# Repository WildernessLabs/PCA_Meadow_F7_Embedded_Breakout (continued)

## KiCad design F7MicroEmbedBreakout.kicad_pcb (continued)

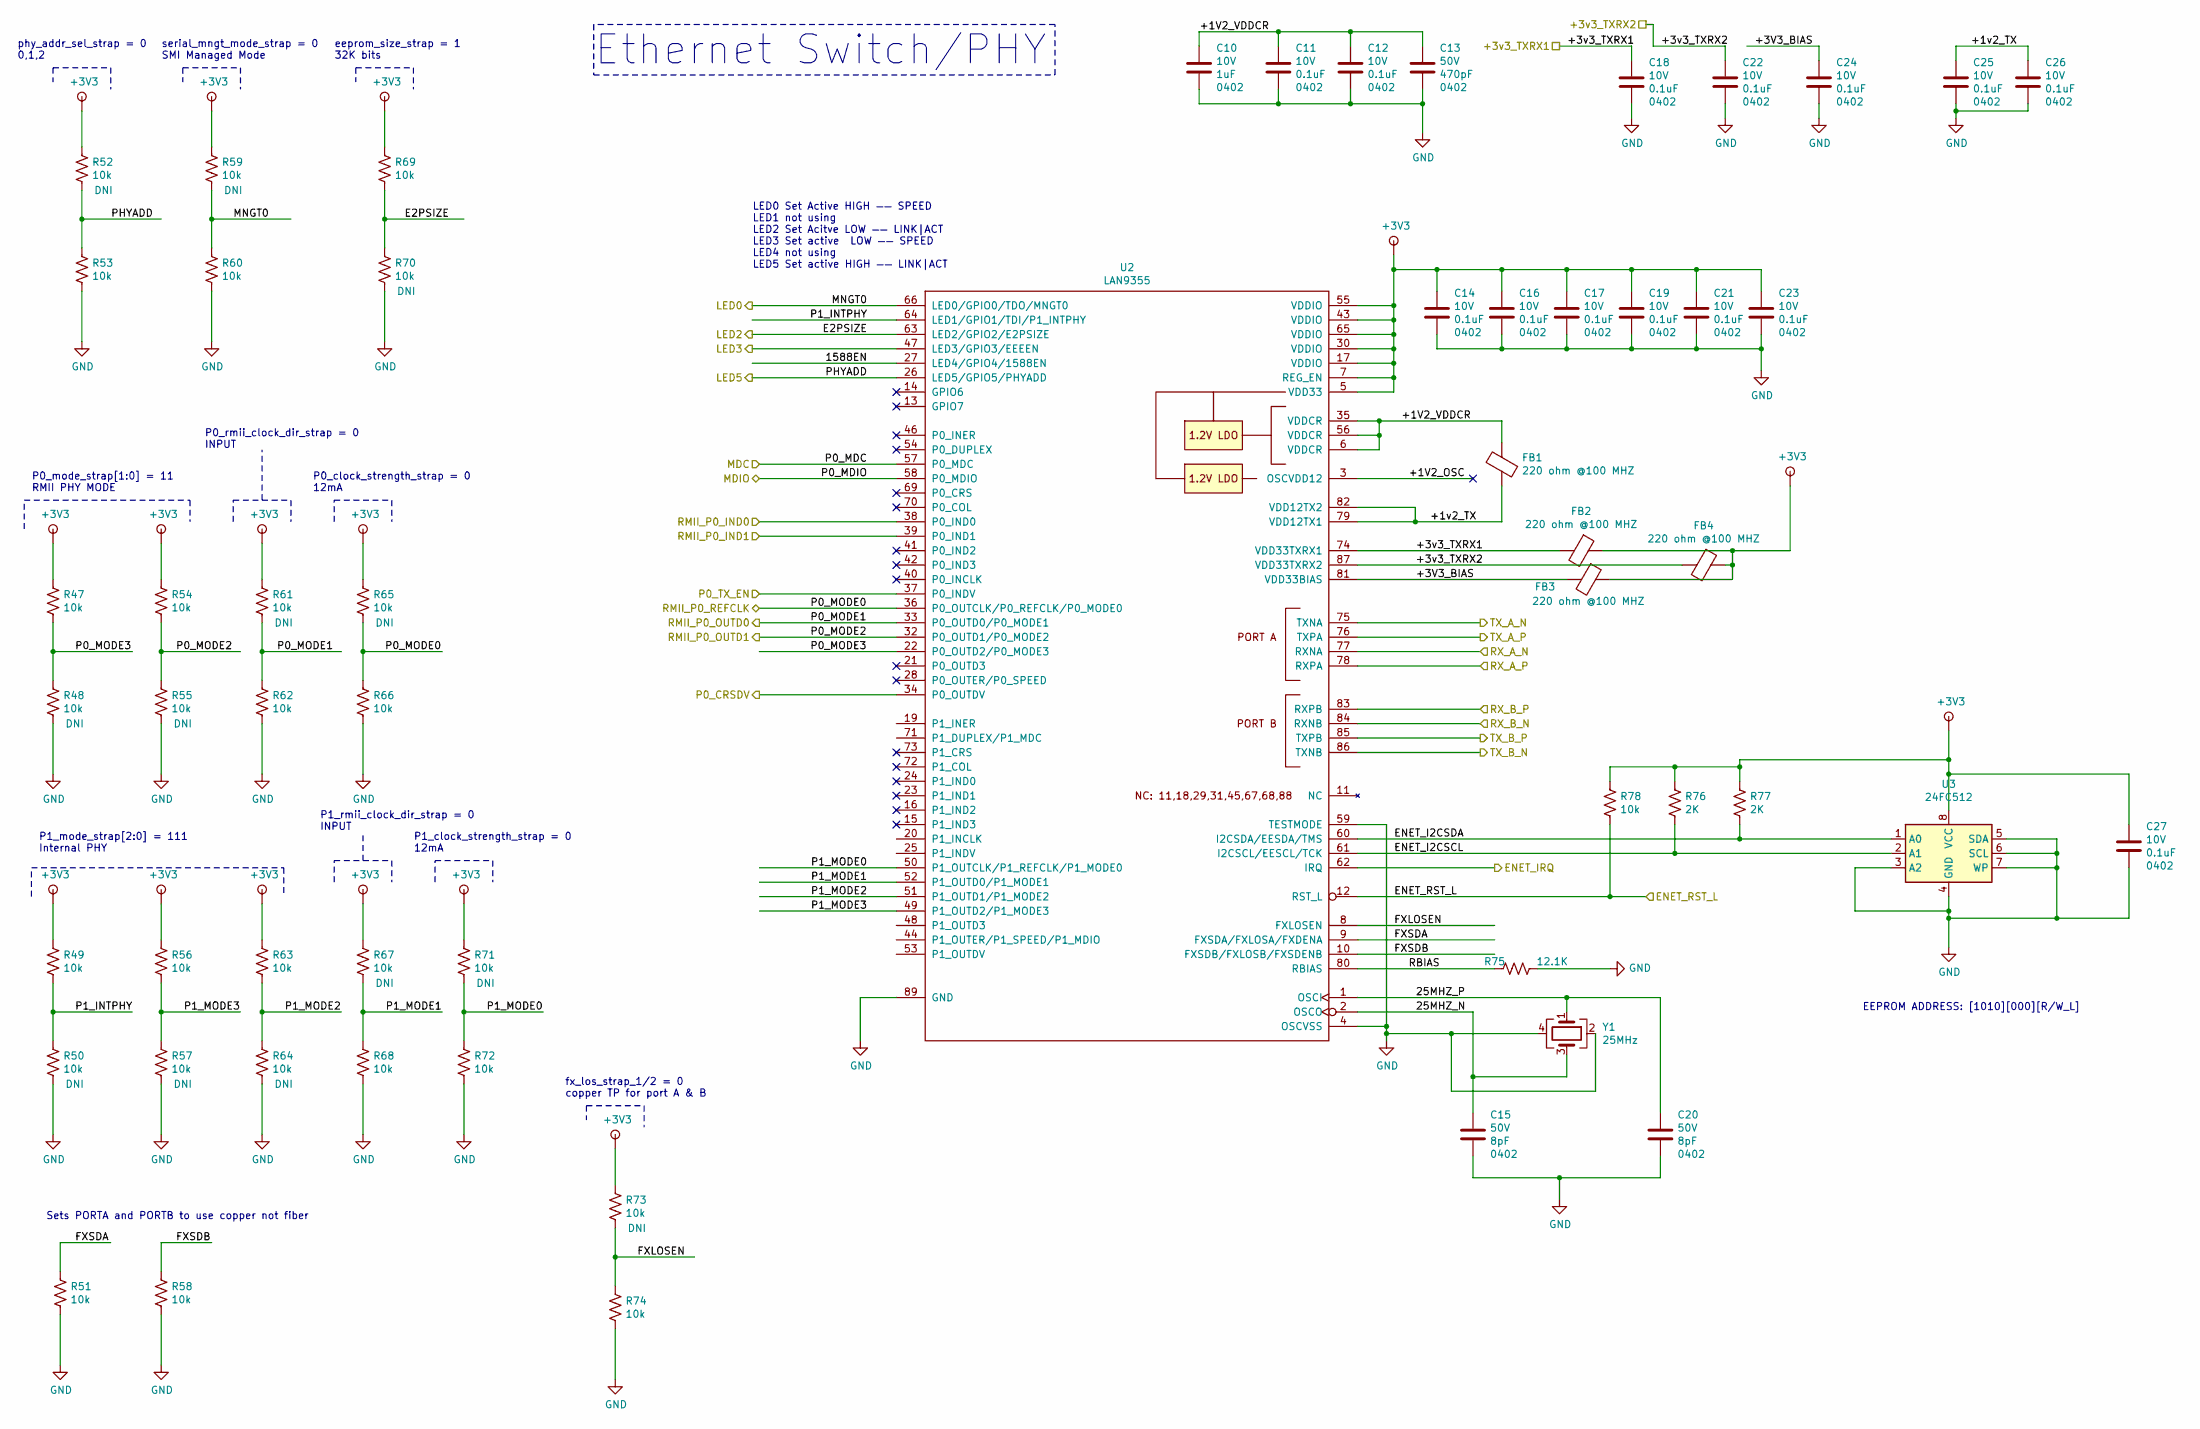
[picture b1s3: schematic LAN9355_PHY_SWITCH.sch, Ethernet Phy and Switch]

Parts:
C10: C_0402_1UF_10V_X5R; C_0402_1005Metric; Voltage 10V; Tolerance 20%
C11, C12, C14, C16, C17, C18, C19, C21, C22, C23, C24, C25, C26, C27: C_0402_0.1UF_10V_X5R; C_0402_1005Metric; Voltage 10V; Tolerance 20%
C13: C_0402_470pF_50V_X5R; C_0402_1005Metric; Voltage 50V; Tolerance 10%
C15, C20: C_0402_8pF_50V_X5R; C_0402_1005Metric; Voltage 50V; Tolerance 0.25pF
FB1, FB2, FB3, FB4: BEAD_BLM18KG221SN1D; R_0603
R47, R48, R49, R50, R51, R52, R53, R54, R55, R56, R57, R58, R59, R60, R61, R62, R63, R64, R65, R66, R67, R68, R69, R70, R71, R72, R73, R74, R78: R_10k_1%_0603; R_0402_1005Metric; Tolerance 1%
R75: R_12K1_1%_0402; R_0402_1005Metric; Tolerance 1%
R76, R77: R_2K_1%_0402; R_0402_1005Metric; Tolerance 1%
U2: LAN9355; QFN-88_EP_12x12_Pitch0.5mm
U3: 24FC512; TSSOP-8_4.4x3mm_P0.65mm
Y1: ABM12W-25.0000MHZ-6-B1U-T3; XTAL_ABM12W-24.0000MHZ-6-B1U-T3

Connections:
+3V3: C14.1, C16.1, C17.1, C19.1, C21.1, C23.1, C27.1, FB2.1, FB3.1, FB4.1, R47.1, R49.1, R52.1, R54.1, R56.1, R59.1, R61.1, R63.1, R65.1, R67.1, R69.1, R71.1, R73.1, R76.1, R77.1, R78.1, U2.5 (VDD33), U2.7 (REG_EN), U2.17 (VDDIO), U2.30 (VDDIO), U2.43 (VDDIO), U2.55 (VDDIO), U2.65 (VDDIO), U3.8 (VCC); also elsewhere on the board
/ENET_SWITCH_PHY/25MHZ_N: C15.1, U2.2 (OSCO), Y1.3
/ENET_SWITCH_PHY/25MHZ_P: C20.1, U2.1 (OSCI), Y1.1
/ENET_SWITCH_PHY/1588EN: U2.27 (LED4/GPIO4/1588EN)
/ENET_SWITCH_PHY/+1V2_OSC: U2.3 (OSCVDD12)
/ENET_SWITCH_PHY/+1V2_VDDCR: C10.1, C11.1, C12.1, C13.1, FB1.2, U2.6 (VDDCR), U2.35 (VDDCR), U2.56 (VDDCR)
/ENET_SWITCH_PHY/+1v2_TX: C25.1, C26.1, FB1.1, U2.79 (VDD12TX1), U2.82 (VDD12TX2)
/ENET_SWITCH_PHY/+3V3_BIAS: C24.1, FB3.2, U2.81 (VDD33BIAS)
/ENET_SWITCH_PHY/+3v3_TXRX1: C18.1, FB2.2, U2.74 (VDD33TXRX1); also elsewhere on the board
/ENET_SWITCH_PHY/+3v3_TXRX2: C22.1, FB4.2, U2.87 (VDD33TXRX2); also elsewhere on the board
/ENET_SWITCH_PHY/ENET_I2CSCL: R76.2, U2.61 (I2CSCL/EESCL/TCK), U3.2 (A1)
/ENET_SWITCH_PHY/ENET_I2CSDA: R77.2, U2.60 (I2CSDA/EESDA/TMS), U3.1 (A0)
/ENET_SWITCH_PHY/FXLOSEN: R73.2, R74.1, U2.8 (FXLOSEN)
/ENET_SWITCH_PHY/FXSDA: R51.1, U2.9 (FXSDA/FXLOSA/FXDENA)
/ENET_SWITCH_PHY/FXSDB: R58.1, U2.10 (FXSDB/FXLOSB/FXSDENB)
/ENET_SWITCH_PHY/P0_MODE3: R47.2, R48.1, U2.22 (P0_OUTD2/P0_MODE3)
/ENET_SWITCH_PHY/P1_INTPHY: R49.2, R50.1, U2.64 (LED1/GPIO1/TDI/P1_INTPHY)
/ENET_SWITCH_PHY/P1_MODE0: R71.2, R72.1, U2.50 (P1_OUTCLK/P1_REFCLK/P1_MODE0)
/ENET_SWITCH_PHY/P1_MODE1: R67.2, R68.1, U2.52 (P1_OUTD0/P1_MODE1)
/ENET_SWITCH_PHY/P1_MODE2: R63.2, R64.1, U2.51 (P1_OUTD1/P1_MODE2)
/ENET_SWITCH_PHY/P1_MODE3: R56.2, R57.1, U2.49 (P1_OUTD2/P1_MODE3)
/ENET_SWITCH_PHY/RBIAS: R75.2, U2.80 (RBIAS)
/ETH_MDIO: U2.58 (P0_MDIO); also elsewhere on the board
/LED0: R59.2, R60.1, U2.66 (LED0/GPIO0/TDO/MNGT0); also elsewhere on the board
/LED2: R69.2, R70.1, U2.63 (LED2/GPIO2/E2PSIZE); also elsewhere on the board
/LED3: U2.47 (LED3/GPIO3/EEEEN); also elsewhere on the board
/LED5: R52.2, R53.1, U2.26 (LED5/GPIO5/PHYADD); also elsewhere on the board
/PB4: U2.62 (IRQ); also elsewhere on the board
/PC0\ETH_MDC\ADC1_IN10: U2.57 (P0_MDC); also elsewhere on the board
/PD5: R78.2, U2.12 (RST_L); also elsewhere on the board
/RMII_CRS_DV: U2.34 (P0_OUTDV); also elsewhere on the board
/RMII_REF_CLK: R65.2, R66.1, U2.36 (P0_OUTCLK/P0_REFCLK/P0_MODE0); also elsewhere on the board
/RMII_RXD0: R61.2, R62.1, U2.33 (P0_OUTD0/P0_MODE1); also elsewhere on the board
/RMII_RXD1: R54.2, R55.1, U2.32 (P0_OUTD1/P0_MODE2); also elsewhere on the board
/RMII_TXD0: U2.38 (P0_IND0); also elsewhere on the board
/RMII_TXD1: U2.39 (P0_IND1); also elsewhere on the board
/RMII_TX_EN: U2.37 (P0_INDV); also elsewhere on the board
/RX_A_N: U2.77 (RXNA); also elsewhere on the board
/RX_A_P: U2.78 (RXPA); also elsewhere on the board
/RX_B_N: U2.84 (RXNB); also elsewhere on the board
/RX_B_P: U2.83 (RXPB); also elsewhere on the board
/TX_A_N: U2.75 (TXNA); also elsewhere on the board
/TX_A_P: U2.76 (TXPA); also elsewhere on the board
/TX_B_N: U2.86 (TXNB); also elsewhere on the board
/TX_B_P: U2.85 (TXPB); also elsewhere on the board
GND: C10.2, C11.2, C12.2, C13.2, C14.2, C15.2, C16.2, C17.2, C18.2, C19.2, C20.2, C21.2, C22.2, C23.2, C24.2, C25.2, C26.2, C27.2, R48.2, R50.2, R51.2, R53.2, R55.2, R57.2, R58.2, R60.2, R62.2, R64.2, R66.2, R68.2, R70.2, R72.2, R74.2, R75.1, U2.4 (OSCVSS), U2.59 (TESTMODE), U2.89 (GND), U3.3 (A2), U3.4 (GND), U3.5 (SDA), U3.6 (SCL), U3.7 (WP), Y1.2, Y1.4; also elsewhere on the board

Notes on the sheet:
Sets PORTA and PORTB to use copper not fiber
EEPROM ADDRESS: [1010][000][R/W_L]
P0_mode_strap[1:0] = 11 RMII PHY MODE
P0_rmii_clock_dir_strap = 0 INPUT
P0_clock_strength_strap = 0 12mA
P1_mode_strap[2:0] = 111 Internal PHY
P1_rmii_clock_dir_strap = 0 INPUT
P1_clock_strength_strap = 0 12mA
phy_addr_sel_strap = 0 0,1,2
fx_los_strap_1/2 = 0 copper TP for port A & B
LED0 Set Active HIGH —— SPEED LED1 not using LED2 Set Acitve LOW —— LINK|ACT LED3 Set active LOW —— SPEED LED4 not using LED5 Set active HIGH —— LINK|ACT
serial_mngt_mode_strap = 0 SMI Managed Mode
eeprom_size_strap = 1 32K bits
Ethernet Switch/PHY

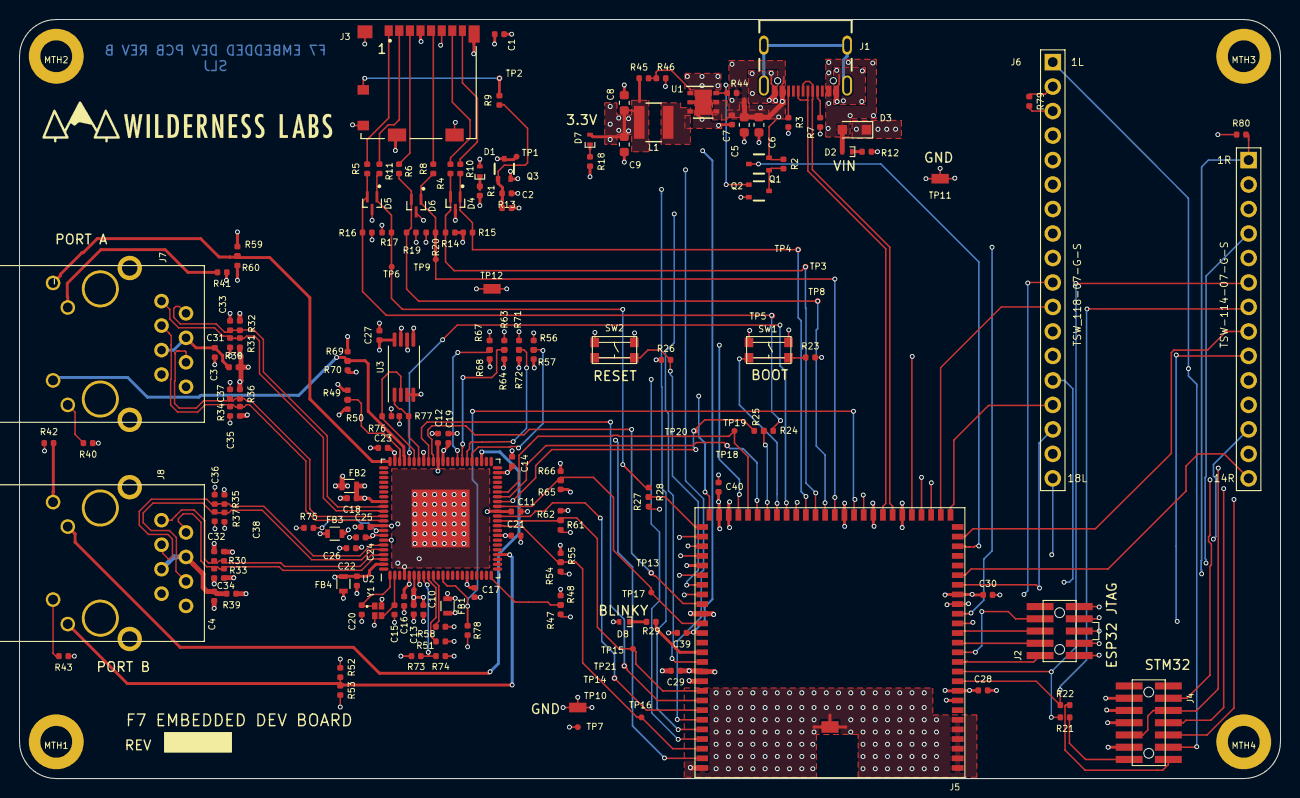
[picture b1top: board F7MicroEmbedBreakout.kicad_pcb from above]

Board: 6 copper layers, 130.8 x 78.7 mm, 175 parts (0 on the bottom side), 120 nets.

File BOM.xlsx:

Reference | Quantity | DNI | Value | Footprint | Datasheet | MF | PN | MF2 | PN2
C1 C28 C29 C30 C39 C40 C7 C14 C16 C17 C19 C21 C23 C18 C22 C24 C25 C26 C11 C12 C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 | 21 |  | C_0402_0.1UF_10V_X5R | Capacitors_SMD:C_0402_1005Metric | ~ | KEMET | C0402C104M8PACTU | Samsung Electro-Mechanics | CL05A104MP5NNNC
C13 | 1 |  | C_0402_470pF_50V_X5R | Capacitors_SMD:C_0402_1005Metric | ~ | Samsung Electro-Mechanics | CL05B471KB5NNNC | KEMET | C0402C471K5RACTU
C2 C10 | 2 |  | C_0402_1UF_10V_X5R | Capacitors_SMD:C_0402_1005Metric | ~ | Yageo | CC0402MRX5R6BB105 | KEMET | C0402C105M8PACTU
C3 C4 | 2 |  | C_0402_0.022UF_50V_X5R | Capacitors_SMD:C_0402_1005Metric | ~ | TDK Corp | CGA2B3X5R1H223K050BB
C31 C33 C35 C37 C32 C34 C36 C38 C15 C20 | 10 |  | C_0402_8pF_50V_X5R | Capacitors_SMD:C_0402_1005Metric | ~ | Yageo | CC0402CRNPO9BN8R0 | Murata | GJM1555C1H8R0CB01D
C6 C8 C9 C5 | 4 |  | C_0603_22UF_10V_X5R | Capacitors_SMD:C_0603_1608Metric | ~ | Murata Electronics North America | GRM188R61A226ME15D | Samsung Electro-Mechanics | CL10A226MPCNUBE
D1 D2 D7 | 3 |  | LED_G_EAST10052GA0 | SLJ_SMT:LED_0402 | https://everlightamericas.com/index.php?controller=attachmen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 | Everlight Electronics Co Ltd | EAST10052GA0
D3 | 1 |  | BAT60J | Diodes_SMD:D_SOD-323_HandSoldering | http://www.st.com/content/ccc/resource/technical/document/da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 | STMicroelectronics | BAT60JFILM
D4 D5 D6 | 3 |  | EGUARD0502BTR | SLJ_SMT:SOT50P160X90-3N | http://www.smc-diodes.com/propdf/eGuard0502B%20N2117%20REV.-.pdf | SMC Diode Solutions | EGUARD0502BTR
D8 | 1 |  | LED_B_EAST1005BA0 | SLJ_SMT:LED_0402 | https://everlightamericas.com/index.php?controller=attachmen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 | Everlight Electronics Co Ltd | EAST1005BA0
FB2 FB4 FB3 FB1 | 4 |  | BEAD_BLM18KG221SN1D | Resistors_SMD:R_0603 | https://media.digikey.com/pdf/Data%20Sheets/Murata%20PDFs/BL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 | Murata | BLM18KG221SN1D
J1 | 1 |  | USB4105-GF-A | SLJ_Connectors:GCT_USB4105-GF-A | https://www.usb.org/sites/default/files/documents/usb_type-c.zip | GCT | USB4105-GF-A
J2 | 1 |  | SAMTEC-FTSH-105-01-X-D | SLJ_Connectors:SAMTEC_FTSH-105-01-X-DV-K-A | http://suddendocs.samtec.com/catalog_english/ftsh_smt.pdf | Samtec Inc. | FTSH-105-01-S-DV-K-P-TR
J3 | 1 |  | 104031-0811 | MOLEX_104031-0811 | https://www.molex.com/pdm_docs/sd/1040310811_sd.pdf | MOLEX | 1040310811
J4 | 1 |  | FTSH-107-01-L-DV-K-A | SLJ_Connectors:SAMTEC_FTSH-107-01-L-DV-K-A | http://suddendocs.samtec.com/catalog_english/ftsh_smt.pdf | Samtec Inc. | FTSH-107-01-L-DV-K-A | Samtec Inc | FTSH-107-01-L-DV-K
J5 | 1 |  | Meadow_Embedded_Module | SLJ_Mechanical:MeadowEmbeded |  | Winderness Labs
J6 | 1 |  | MicroF7Meadow | SLJ_Mechanical:MeadowF7Micro
J7 J8 | 2 |  | J0011D01BNL | SLJ_Connectors:RJ45_J0011D01BNL | https://productfinder.pulseeng.com/doc_type/WEB301/doc_num/J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 | Pulse Electronics Network | J0011D01BNL
L1 | 1 |  | L_3.3uH_2.4A_SMT_4x4 | SLJ_SMT:Inductor_Abracon_ASPI-4030 | https://abracon.com/Magnetics/power/ASPI-4030S.pdf | Abracon LLC | ASPI-4030S-3R3M-T
MTH1 MTH2 MTH3 MTH4 | 4 | DNI | MTH_3.3MM_5.7MM | SLJ_Mechanical:MTH_3.3MM_5.7MM
Q2 | 1 |  | N-CH_DMG1012UW-7 | SLJ_SMT:SC-70FL | https://www.diodes.com/assets/Datasheets/ds31859.pdf | Diodes Incorporated | DMG1012UW-7
Q3 Q1 | 2 |  | MCH3383-TL-W | SLJ_SMT:SC-70FL | https://www.onsemi.cn/PowerSolutions/document/MCH3383-D.PDF | ON Semiconductor | MCH3383-TL-W
R1 R18 R12 | 3 |  | R_1K_1%_0402 | Resistor_SMD:R_0402_1005Metric | ~ | Yageo | RC0402FR-071KL | Vishay Dale | CRCW04021K00FKEDC
R11 R5 R4 R10 R6 R8 | 6 |  | R_20_1%_0402 | Resistor_SMD:R_0402_1005Metric | ~ | Stackpole Electronics Inc | RMCF0402FT20R0 | Vishay Dale | CRCW040220R0FKEDC
R13 R9 | 2 |  | R_100K_1%_0402 | Resistor_SMD:R_0402_1005Metric | ~ | Panasonic Electronic Components | ERJ-2RKF1003X | Stackpole Electronics Inc | RMCF0402FT100K
R14 R15 R16 R17 R19 R20 R2 R44 | 8 |  | R_10K_1%_0402 | Resistor_SMD:R_0402_1005Metric | ~ | Yageo | AC0402FR-0710KL | Stackpole Electronics Inc | RMCF0402FT10K0
R22 R21 | 2 |  | R_0_1%_0402 | Resistor_SMD:R_0402_1005Metric | ~ | Stackpole Electronics Inc | RMCF0402ZT0R00 | Vishay Dale | CRCW04020000Z0ED
R23 R26 | 2 |  | R_10K_1%_0402-SLJ_Resistor_0402 | Resistor_SMD:R_0402_1005Metric |  | Yageo | AC0402FR-0710KL | Stackpole Electronics Inc | RMCF0402FT10K0
R29 R43 R42 R41 R40 | 5 |  | R_300_1%_0402 | Resistor_SMD:R_0402_1005Metric | ~ | Yageo | RC0402FR-07300RL | Stackpole Electronics Inc | RMCF0402FT300R
R3 R7 | 2 |  | R_5K1_1%_0402 | Resistor_SMD:R_0402_1005Metric | ~ | Yageo | RC0402FR-075K1L | Stackpole Electronics Inc | RMCF0402FT5K10
R31 R32 R34 R36 R30 R33 R35 R37 | 8 |  | R_49R9_1%_0402 | Resistor_SMD:R_0402_1005Metric | ~ | Yageo | RC0402FR-0749R9L | Panasonic | ERJ-2RKF49R9X
R38 R39 R24 R25 R28 R27 R79 R80 | 8 |  | R_0R_1%_0603 | Resistor_SMD:R_0402_1005Metric | ~ | Yageo | RC0603JR-070RL | Panasonic | ERJ-3GEY0R00V
R45 | 1 |  | R_24K9_1%_0402 | Resistor_SMD:R_0402_1005Metric | ~ | Yageo | RC0402FR-0724K9L | Stackpole Electronics Inc | RMCF0402FT24K9
R46 | 1 |  | R_8K06_1%_0402 | Resistor_SMD:R_0402_1005Metric | ~ | Yageo | RC0402FR-078K06L | Stackpole Electronics Inc | RMCF0402FT8K06
R47 R48 R54 R55 R61 R62 R65 R66 R56 R57 R63 R64 R67 R68 R71 R72 R51 R58 R49 R50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 | 29 |  | R_10k_1%_0603 | Resistor_SMD:R_0402_1005Metric | ~ | Yageo | RC0603FR-0710KL | Stackpole | RNCP0603FTD10K0
R75 | 1 |  | R_12K1_1%_0402 | Resistor_SMD:R_0402_1005Metric | ~ | Yageo | RC0402FR-0712K1L | Stackpole Electronics Inc | RMCF0402FT12K1
R76 R77 | 2 |  | R_2K_1%_0402 | Resistor_SMD:R_0402_1005Metric | ~ | Yageo | RC0402FR-072KL | Vishay Dale | CRCW04022K00FKED
SW1 SW2 | 2 |  | SW_KMR211NG | SLJ_Mechanical:KMR211NG | https://dznh3ojzb2azq.cloudfront.net/products/Tactile/KMR2/d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 | C&K | KMR211NG LFS
TP10 TP11 TP12 | 3 |  | TestPoint_SMT_loop_1X1.8MM | SLJ_Mechanical:TP_S2761-46R | ~
TP3 TP4 TP5 TP6 TP8 TP9 TP1 TP2 TP7 TP14 TP15 TP16 TP17 TP18 TP19 TP20 TP13 TP21 | 18 | DNI | TestPoint_SMT_25mil | SLJ_Mechanical:PAD_RD_0.63 | ~
U1 | 1 |  | NCP1597A | Housings_DFN_QFN:DFN-6-1EP_3x3mm_Pitch0.95mm | https://www.onsemi.com/pub/Collateral/NCP1597-D.PDF | ON Semiconductor | NCP1597AMNTWG
U2 | 1 |  | LAN9355 | SLJ_QFN:QFN-88_EP_12x12_Pitch0.5mm | http://ww1.microchip.com/downloads/en/DeviceDoc/00001927A.pdf |  | LAN9355/ML
U3 | 1 |  | 24FC512 | Package_SO:TSSOP-8_4.4x3mm_P0.65mm | https://ww1.microchip.com/downloads/en/DeviceDoc/21754M.pdf | Microchip Technology | 24FC512T-I/ST
Y1 | 1 |  | ABM12W-25.0000MHZ-6-B1U-T3 | SLJ_Crystals_Osc:XTAL_ABM12W-24.0000MHZ-6-B1U-T3 | https://abracon.com/Resonators/ABM12W.pdf | Abracon LLC | ABM12W-25.0000MHZ-6-B1U-T3

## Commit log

2020-08-24 started working on REv B
2020-09-07 updated almost complete
2020-09-07 trying to get BOM
2020-09-07 fixing library issues
2020-09-08 Added Gerbers and BOM. Ready to release
2020-09-09 moved gerbers to a different folder
2020-09-12 Fixed some issues in the bregers from the board house
2020-09-13 updated 3d files and readme
2020-09-15 Updated gerbers to fix error Rev B2
2020-10-22 add ds_store to gitignore
2020-12-21 Updated BOM with spare parts
    BOM -> Alt
    C0402C104M8PACTU -> C0402C104M8PAC7867
    AC0402FR-0710KL -> RC0402FR-0710KL
    RMCF0402ZT0R00 -> RC0402JR-070RL
2021-01-14 Added comments to the pdf schematic of a BUG
